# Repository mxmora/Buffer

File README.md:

# Buffer

Git hub project for buffer tutorial

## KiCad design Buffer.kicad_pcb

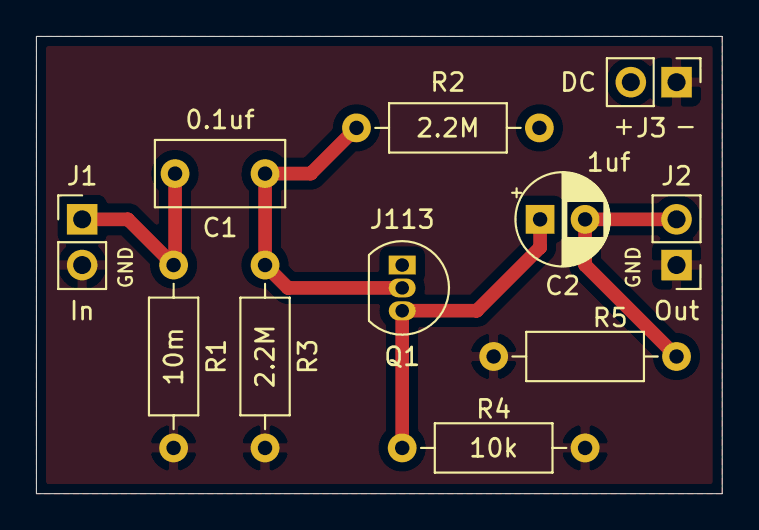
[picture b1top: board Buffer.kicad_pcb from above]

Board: 2 copper layers, 38.1 x 25.4 mm, 11 parts (0 on the bottom side), 6 nets.

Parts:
C1: 0.1uf; C_Rect_L7.0mm_W3.5mm_P5.00mm
C2: 1uf; CP_Radial_D5.0mm_P2.50mm
J1: In; PinHeader_1x02_P2.54mm_Vertical
J2: Out; PinHeader_1x02_P2.54mm_Vertical
J3: DC; PinHeader_1x02_P2.54mm_Vertical
Q1: J113; TO-92_Inline
R1: 10m; R_Axial_DIN0207_L6.3mm_D2.5mm_P10.16mm_Horizontal
R2, R3: 2.2M; R_Axial_DIN0207_L6.3mm_D2.5mm_P10.16mm_Horizontal
R4: 10k; R_Axial_DIN0207_L6.3mm_D2.5mm_P10.16mm_Horizontal
R5: 100k; R_Axial_DIN0207_L6.3mm_D2.5mm_P10.16mm_Horizontal

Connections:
+9V: J3.2, Q1.1, R2.1
GND: J1.2, J2.1, J3.1, R1.2, R3.2, R4.2, R5.2
unnamed: C1.1, Q1.2, R2.2, R3.1
unnamed: C1.2, J1.1, R1.1
unnamed: C2.1, Q1.3, R4.1
unnamed: C2.2, J2.2, R5.1

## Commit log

2019-07-27 first check in
